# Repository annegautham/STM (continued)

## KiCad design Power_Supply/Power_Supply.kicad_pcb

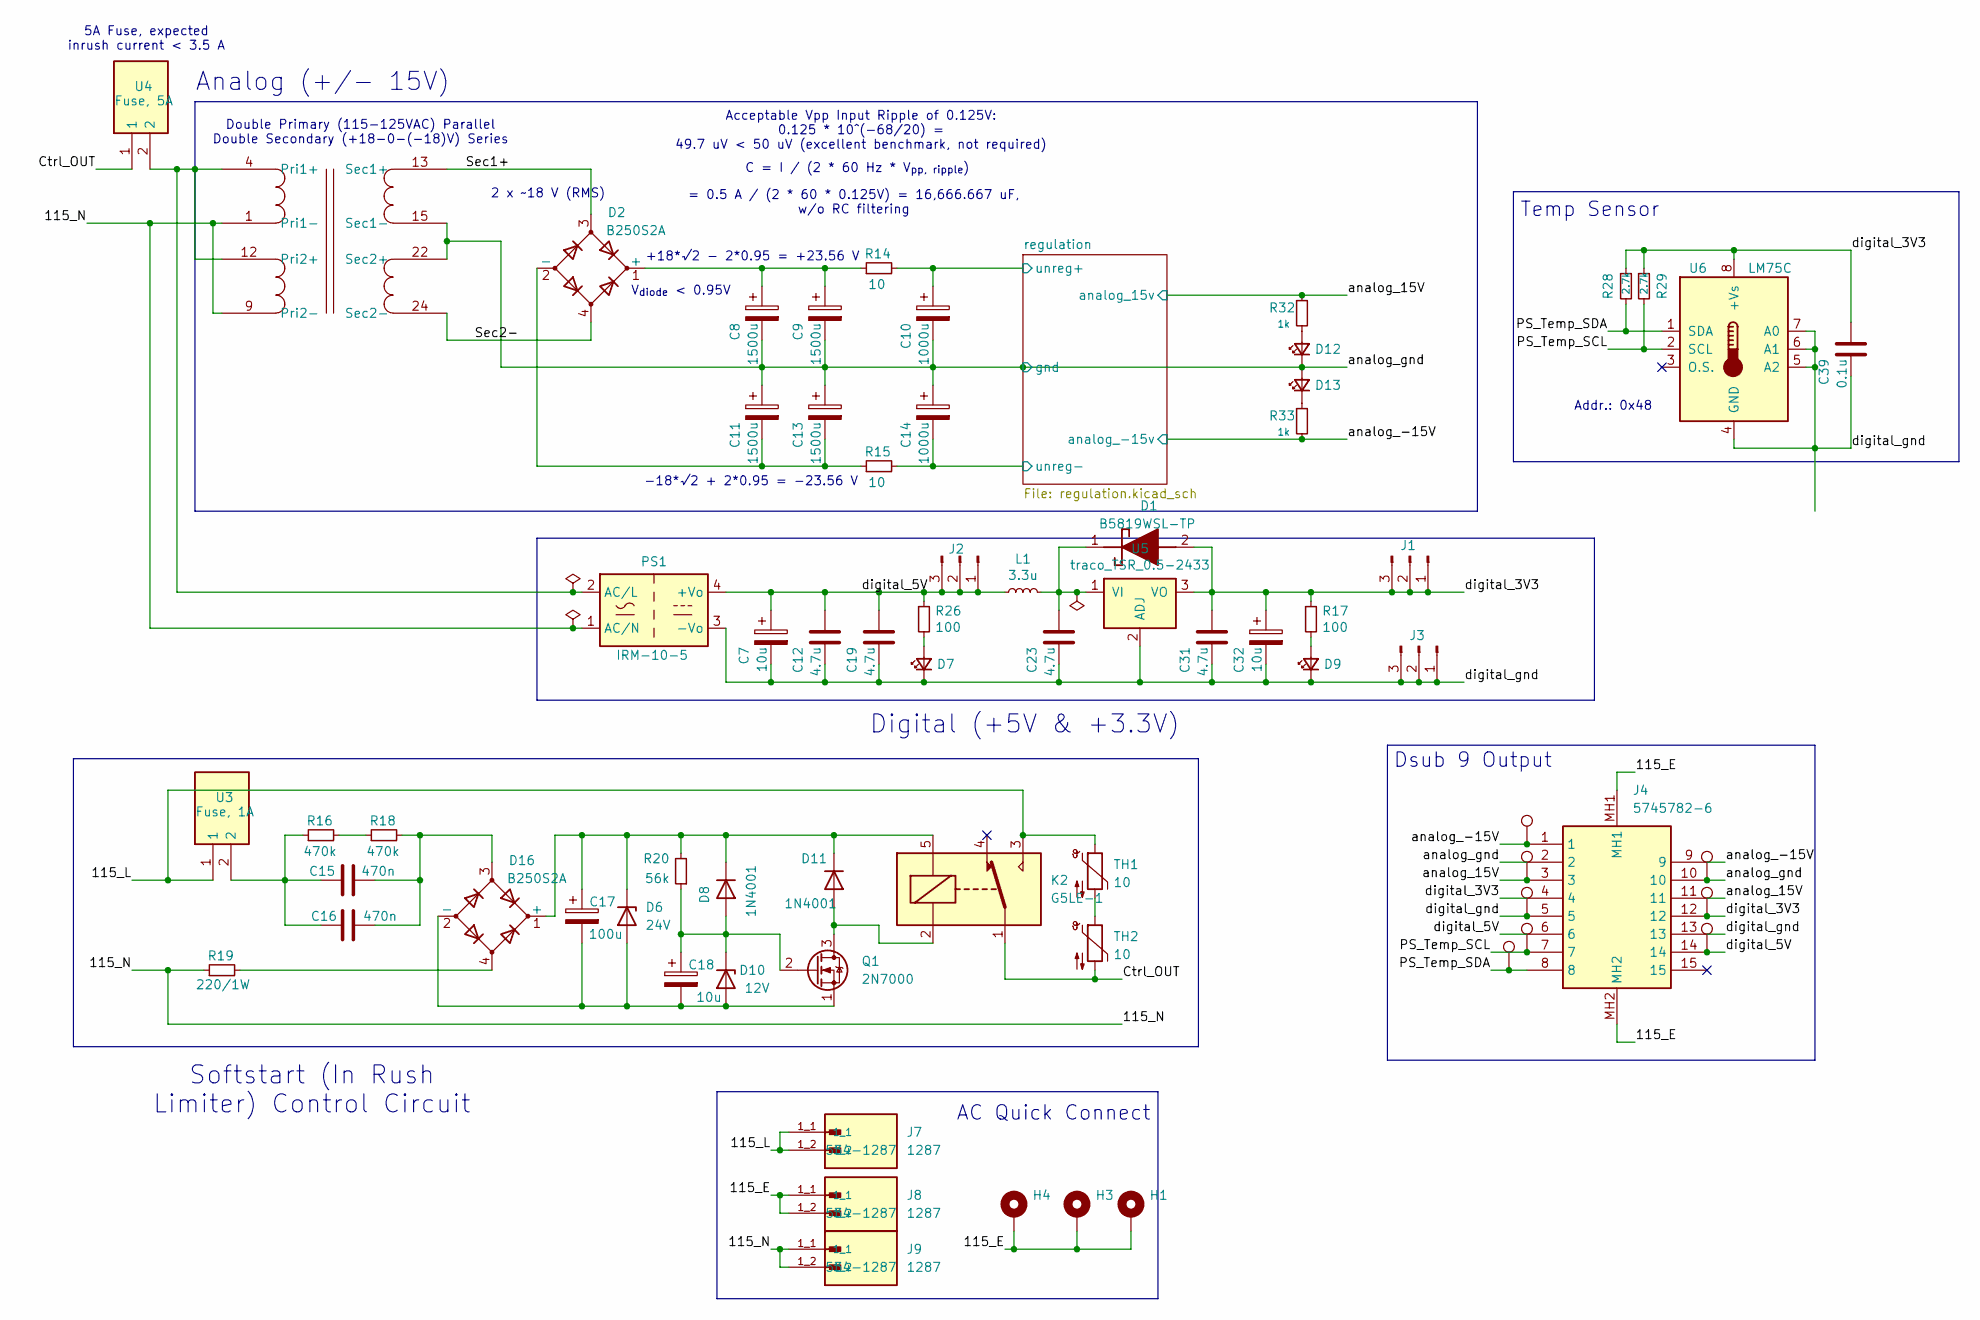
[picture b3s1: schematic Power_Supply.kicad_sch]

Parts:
C7, C32: 10u; CP_EIA-7343-31_Kemet-D; Mouser Part Number 80-T491D106K025
C8, C9, C11, C13: 1500u; CP_Radial_D12.5mm_P5.00mm_+Better; Mouser Part Number 647-UHW1H152MHD
C10, C14: 1000u; CP_Radial_D12.5mm_P5.00mm_+Better; Mouser Part Number 647-UHW1H102MHD
C12, C19, C23, C31: 4.7u; C_0603_1608Metric; Mouser Part Number 187-CL10A475KO8NQNC
C15, C16: 470n; CAP_R46KN347000N0M_KEM; Mouser Part Number 80-R46KN347000N0M
C17: 100u; C_Radial_D10.0mm_H12.5mm_P5.00mm; Mouser Part Number 594-2222-140-50101
C18: 10u; CP_Radial_D5.0mm_P2.00mm; Mouser Part Number 710-860010372001
C39: 0.1u; C_0603_1608Metric; Mouser Part Number 80-C0603C104J1RAUTO7
D1: B5819WSL-TP; SODFL2512X90N; Mouser Part Number 833-B5819WSL-TP
D2, D16: B250S2A; P20_SO-DIL-Slim; Mouser Part Number 637-B250S2A-SLIM
D6: 24V; D_SOD-123; Mouser Part Number 863-SZMMSZ4709T1G
D7, D9, D12, D13: LED_Small; LED_0603_1608Metric
D8, D11: 1N4001; D_DO-41_SOD81_P10.16mm_Horizontal; Mouser Part Number 637-1N4001
D10: 12V; D_SOD-123; Mouser Part Number 78-MMSZ4699-HE3_A-08
H1, H3, H4: MountingHole_Pad; MountingHole_3.2mm_M3_Pad_Via
J1, J2, J3: Conn_01x03_Pin; PinHeader_1x03_P2.54mm_Vertical
J4: 5745782-6; 57457826; Mouser Part Number 571-5745782-6
J7, J8, J9: 1287; KEYSTONE_1287; PARTREV F; Mouser Part Number 534-1287
K2: G5LE-1; Relay_SPDT_Omron-G5LE-1; Mouser Part Number 653-G5LE-1-SDC24
L1: 3.3u; IND_BOURNS_SRR1280; Mouser Part Number 652-SRR1280-3R3Y
PS1: IRM-10-5; Converter_ACDC_MeanWell_IRM-10-xx_THT; Mouser Part Number 709-IRM10-5
Q1: 2N7000; TO-92_Inline; Mouser Part Number 512-2N7000
R14, R15: 10; R_1206_3216Metric; Mouser Part Number 71-RCC120610R0JNEA
R16, R18: 470k; R_Axial_DIN0207_L6.3mm_D2.5mm_P15.24mm_Horizontal; Mouser Part Number 71-CCF07470KJKE36
R17, R26: 100; R_0805_2012Metric; Mouser Part Number 710-560112120020
R19: 220/1W; R_2512_6332Metric; Mouser Part Number 279-3520220RJT
R20: 56k; R_0805_2012Metric; Mouser Part Number 755-ESR10EZPF5602
R28, R29: 2.7k; R_0805_2012Metric; Mouser Part Number 603-AA0805JR-072K7L
R32, R33: 1k; R_0805_2012Metric
T1: FLN_40_18
TH1, TH2: 10; R_Axial_DIN0204_L3.6mm_D1.6mm_P5.08mm_Horizontal; Mouser Part Number 995-SL10-10002
TP1, TP2, TP3, TP4, TP5, TP6, TP7, TP8: TestPoint; TestPoint_Loop_D1.80mm_Drill1.0mm_Beaded; Mouser Part Number 534-5005
U3: Fuse, 1A; 0PTF0078P; Mouser Part Number 576-0PTF0078P
U4: Fuse, 5A; 0PTF0078P; Mouser Part Number 576-0PTF0078P
U5: traco_TSR_0.5-2433; TSR-0.5-2433; Mouser Part Number 495-TSR0.5-2433
U6: LM75C; SOIC-8_3.9x4.9mm_P1.27mm; Mouser Part Number 700-LM75BIM-3+

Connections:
/115_E: H1.1, H3.1, H4.1, J4.MH1, J4.MH2, J8.1_1, J8.1_2
/115_L: J7.1_1, J7.1_2, K2.3, TH1.1, U3.1
/115_N: J9.1_1, J9.1_2, PS1.1 (AC/N), R19.1, T1.1 (Pri1-), T1.9 (Pri2-)
/Ctrl_OUT: K2.1, TH2.2, U4.1
/PS_Temp_SCL: J4.7, R29.2, TP7.1, U6.2 (SCL)
/PS_Temp_SDA: J4.8, R28.2, TP8.1, U6.1 (SDA)
/Sec1+: D2.3, T1.13 (Sec1+)
/Sec2-: D2.4, T1.24 (Sec2-)
/analog_15V: J4.3, J4.11, R32.1, TP3.1; also elsewhere on the board
/analog_gnd: C8.2, C9.2, C10.2, C11.1, C13.1, C14.1, D12.1 (K), D13.2 (A), J4.2, J4.10, T1.15 (Sec1-), T1.22 (Sec2+), TP2.1; also elsewhere on the board
/digital_3V3: C31.1, C32.1, C39.1, D1.2 (A), J1.1, J1.2, J1.3, J4.4, J4.12, R17.1, R28.1, R29.1, TP4.1, U5.3 (VO), U6.8 (+Vs)
/digital_5V: C7.1, C12.1, C19.1, J2.1, J2.2, J2.3, J4.6, J4.14, L1.1, PS1.4 (+Vo), R26.1, TP6.1
/digital_gnd: C7.2, C12.2, C19.2, C23.2, C31.2, C32.2, C39.2, D7.1 (K), D9.1 (K), J3.1, J3.2, J3.3, J4.5, J4.13, PS1.3 (-Vo), TP5.1, U5.2 (ADJ), U6.4 (GND), U6.5 (A2), U6.6 (A1), U6.7 (A0)
/regulation/unreg+: C10.1, R14.2; also elsewhere on the board
/regulation/unreg-: C14.2, R15.2; also elsewhere on the board
unnamed: C15.1, C16.1, R16.1, U3.2
unnamed: C15.2, C16.2, D16.3, R18.2
unnamed: C23.1, D1.1 (K), L1.2, U5.1 (VI)
unnamed: C8.1, C9.1, D2.1 (+), R14.1
unnamed: C11.2, C13.2, D2.2 (-), R15.1
unnamed: D7.2 (A), R26.2
unnamed: D9.2 (A), R17.2
unnamed: C17.2, C18.2, D6.2 (A), D10.2 (A), D16.2 (-), Q1.1 (S)
unnamed: C18.1, D8.2 (A), D10.1 (K), Q1.2 (G), R20.1
unnamed: D11.2 (A), K2.2, Q1.3 (D)
unnamed: C17.1, D6.1 (K), D8.1 (K), D11.1 (K), D16.1 (+), K2.5, R20.2
unnamed: D12.2 (A), R32.2
unnamed: D13.1 (K), R33.1
unnamed: D16.4, R19.2
unnamed: PS1.2 (AC/L), T1.4 (Pri1+), T1.12 (Pri2+), U4.2
unnamed: R16.2, R18.1
unnamed: TH1.2, TH2.1

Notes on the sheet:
Dsub 9 Output
Addr.: 0x48
Analog (+/- 15V)
5A Fuse, expected inrush current < 3.5 A
Acceptable Vpp Input Ripple of 0.125V: 0.125 * 10^(-68/20) = 49.7 uV < 50 uV (excellent benchmark, not required)
Double Primary (115-125VAC) Parallel Double Secondary (+18-0-(-18)V) Series
Softstart (In Rush Limiter) Control Circuit
-18*√2 + 2*0.95 = -23.56 V
C = I / (2 * 60 Hz * V_{pp, ripple})
V_{diode} < 0.95V
AC Quick Connect
2 x ~18 V (RMS)
Temp Sensor
+18*√2 - 2*0.95 = +23.56 V
Digital (+5V & +3.3V)
= 0.5 A / (2 * 60 * 0.125V) = 16,666.667 uF, w/o RC filtering

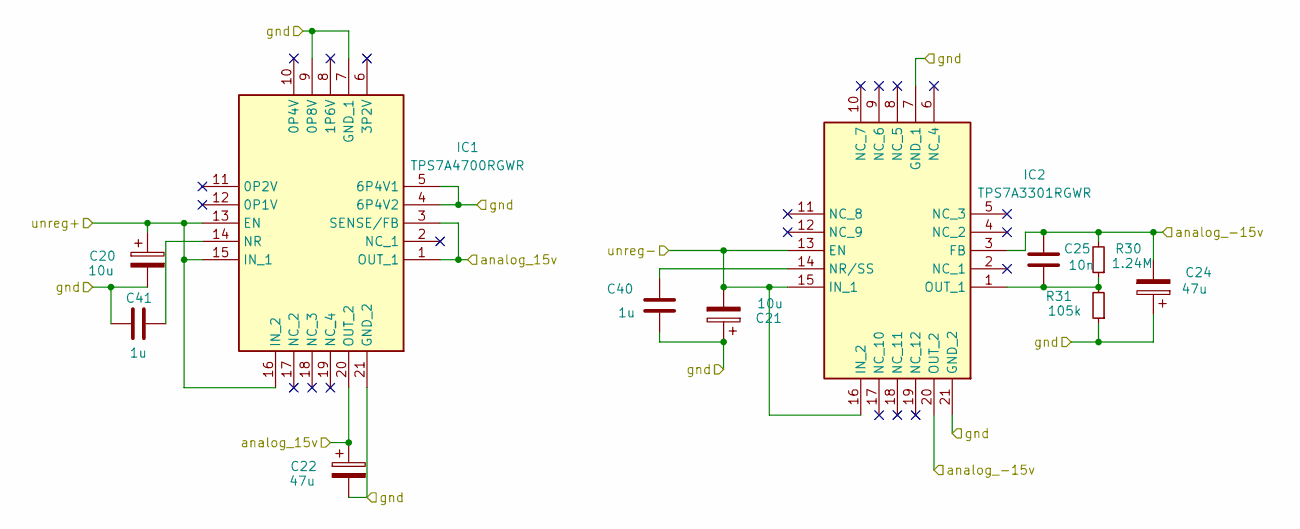
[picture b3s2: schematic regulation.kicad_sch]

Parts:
C20, C21: 10u; CP_EIA-7343-31_Kemet-D; Mouser Part Number 80-T491D106K025
C22, C24: 47u; CP_EIA-7343-31_Kemet-D; Mouser Part Number 80-T491D476K020
C25: 10n; C_0603_1608Metric; Mouser Part Number 581-06033C103KAZ2A
C40, C41: 1u; C_0603_1608Metric; Mouser Part Number 963-MLASU168SB5105KT
IC1: TPS7A4700RGWR; QFN65P500X500X100-21N-D; Mouser Part Number 595-TPS7A4700RGWR
IC2: TPS7A3301RGWR; QFN65P500X500X100-21N-D; Mouser Part Number 595-TPS7A3301RGWR
R30: 1.24M; R_0805_2012Metric; Mouser Part Number 71-CRCW08051M24FKEA
R31: 105k; R_0805_2012Metric; Mouser Part Number 279-RQ73C2A105KBTD

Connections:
/analog_15V: C22.1, IC1.1 (OUT_1), IC1.3 (SENSE/FB), IC1.20 (OUT_2); also elsewhere on the board
/analog_gnd: C20.2, C21.1, C22.2, C24.1, C40.2, C41.2, IC1.4 (6P4V2), IC1.5 (6P4V1), IC1.7 (GND_1), IC1.9 (0P8V), IC1.21 (GND_2), IC2.7 (GND_1), IC2.21 (GND_2), R31.1; also elsewhere on the board
/regulation/unreg+: C20.1, IC1.13 (EN), IC1.15 (IN_1), IC1.16 (IN_2); also elsewhere on the board
/regulation/unreg-: C21.2, IC2.13 (EN), IC2.15 (IN_1), IC2.16 (IN_2); also elsewhere on the board
unnamed: C41.1, IC1.14 (NR)
unnamed: C40.1, IC2.14 (NR/SS)

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
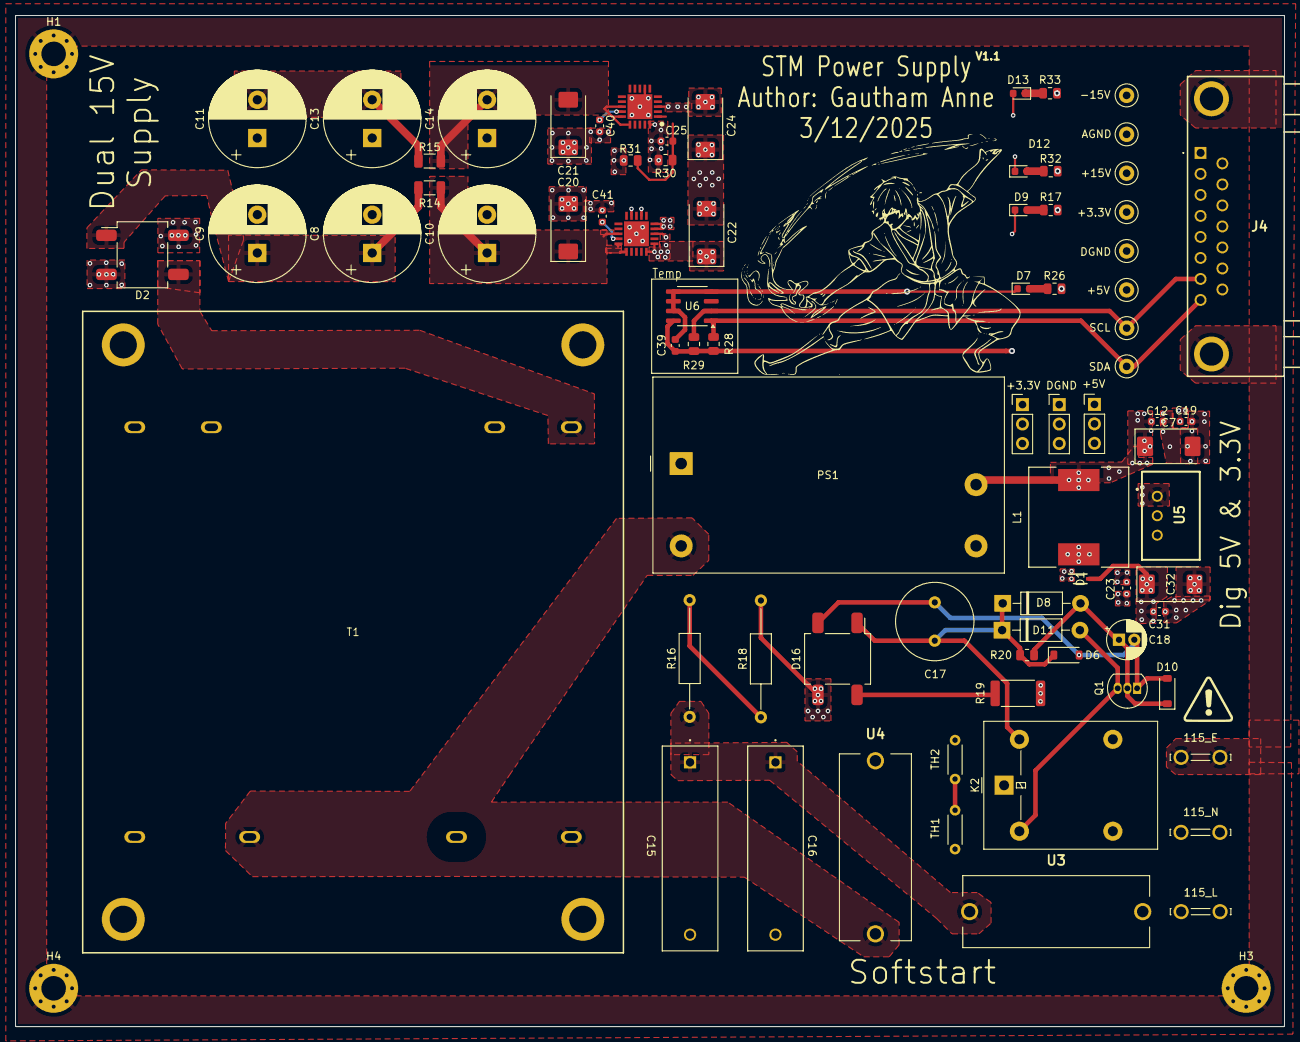
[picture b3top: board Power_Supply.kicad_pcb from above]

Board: 4 copper layers, 165.7 x 132.0 mm, 80 parts (0 on the bottom side), 36 nets.

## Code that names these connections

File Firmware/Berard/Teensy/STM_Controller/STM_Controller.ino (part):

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
All GNDs -> Teensy GND
+5V -> Vin
~CS_DAC -> pin 20
~LDAC -> pin 17
~CS_ADC -> pin 21
CNV -> pin 4
BUSY -> pin 3
MISO_ADC -> pin 12
MOSI_DAC -> pin 11
Serial indicator LED -> pin 0
Tunneling indicator LED -> pin 1
SCK_ADC and SCK_DAC -> pin 13.

*/
/**************************************************************************/


// Pin definitions:
#define CS_DAC 20                          // DAC chip select pin
#define LDAC 17                            // Load DAC pin, not currently used
#define CS_ADC 21                          // ADC chip select pin
#define CNV 4                              // ADC CNV pin - initiates a conversion
#define BUSY 3                             // ADC BUSY pin
#define SERIAL_LED 0                       // Indicates serial data transmission
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#define IMAGE_PIXELS 512                   // Scan size in pixels
#define LINE_RATE 1                        // Number of scan lines/second
#define SETPOINT 328 // 1 nA               // Tunneling current setpoint in LSBs
#define BIAS 328 // 100 mV                 // Sample bias in LSBs
#define KP 0                               // Proportional gain
#define KI 300000                          // Integral gain

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
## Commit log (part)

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2025-02-08 pre amp addition
2025-02-12 tunneling amp v1.0 commit
2025-02-17 Simulations!
2025-02-18 Sent in V1.0 to JLC
2025-02-18 Checking!
2025-03-03 Power Supply Requirements
2025-04-02 updates to Spice Model, Power Supply Design
2025-04-04 Enclosure CAD V1
2025-04-07 Analog Circuit V1.0
2025-04-13 Mainboard grind
2025-04-13 cleanupper
2025-04-13 Project Plan
2025-04-18 CAD updates
2025-04-21 mainboard stuff!
2025-04-23 updates! scan head cad
2025-04-29 working mainboard push!
2025-04-29 more push
2025-04-30 mainboard working commits!
2025-05-01 more pushing!
2025-05-02 final assembly updates!
2025-05-02 bom updates!
2025-05-03 mainboard update
2025-05-03 readme
2025-05-05 Added berard firmware files
2025-05-08 cad update
2025-05-16 firmware updates!
2025-05-16 collet stl
2025-05-16 backend initial version
2025-05-18 collet stls
2025-05-18 directory updates
2025-05-19 codey code
2025-05-22 Initial backend files
2025-05-22 WIP: stashing before merging with g's remote changes to push backend v1
2025-05-22 backend started, compiles
2025-05-22 firmware v1
2025-05-22 foldering
2025-05-25 updates!
2025-05-27 server fixes but still doesn't work
2025-05-28 grr code code code
2025-05-28 cad work
2025-05-28 rebasing
2025-05-28 main
2025-05-28 top cover stl
2025-05-28 backend dev
2025-05-29 caddy cad updates
2025-05-30 control loopsies
2025-05-30 WIP: backend communication
2025-05-30 GUI works and can send and recieve commands
2025-05-31 serial data works
2025-06-01 adding platform.io teensy version w/ new spi libs
2025-06-01 gui added commands ME MP MN and button interaction
2025-06-02 changed server.cpp
2025-06-02 teensy can recieve commands, zach eduroam version
2025-06-02 reorganized files
2025-06-03 working stepper comms
2025-06-11 updates to DAC + ADC Libraries
2025-06-19 spice model uodates
2025-06-19 poster update!
2025-06-19 poster!
2025-06-19 readme!
2025-07-18 mainboard updates
2025-11-16 documentation updartes
2026-01-07 final
